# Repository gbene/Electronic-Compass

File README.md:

# Readme

This is the readme file for the Electronic Compass (E.C.) project. This project has the aim to create a low-cost, open-source electronic geological compass. This repository has the objective to document and share the hardware construction process and software development needed. 

The planned compass features are:

+ Measure dip and dip direction of a plane
+ Measure strike slip, trend and plunge
+ Different measures profiles
+ Automatic txt files save
+ Acceletometer and magnetometer calibration
+ More to come!

## Licences
Since the E.C. project covers hardware and software licences that cover both are necessary. You can find the choosen licences in the "Licences folder" in PDF and .txt format.

| Type | License name | Source link | 
| :----: |:----: | :----:|
| **Software** | GNU General Public License v3.0 or later | [SPDX](https://spdx.org/licenses/GPL-3.0-or-later.html) |
| **Hardware** | CERN-OHL-S-2.0 or any later version | [OHWR](https://ohwr.org/cern_ohl_s_v2.txt) |

Table: Licences used

The copyrights to both hardware and software are explicited in the copyright.pdf and copyright.md files and the original copies are stored in the License folder. If you want to apply any kind of change you **always need to log it in the changes.md file** and include all the original source and copyright files as per licences.

## Components list

The Electronic Compass components are searched to be the most cost-effective and easy to solder available that I could find. I provide the links from where the components are purchased but some are europe based (mostly Germany) so check if worldwide shipping is convenient or not.

| Component Name | Quantity | Price | Link |
|:---|:----:|:----:| ---: |
| Adafruit adalogger M0 | x1 | 26€ | [ThePiHut](https://thepihut.com/products/adafruit-feather-m0-adalogger) |
| GY-61 ADXL335 acceletometer | x1 | €6.79 | [AZ-Delivery](https://www.az-delivery.de/en/products/gy-61-adxl335-beschleunigungssensor-3-axis-neigungswinkel-modul-1?variant=20332875546720) |
| 128x32 Oled display | x1 | €6.29 | [AZ-Delivery](https://thepihut.com/products/adafruit-feather-m0-adalogger) |
| GY-271 QMC5883L magnetometer | x1 | €5.79 | [AZ-Delivery](https://www.az-delivery.de/en/products/gy-271-kompassmodul-kompass-magnet-sensor-fuer-arduino-und-raspberry-pi?variant=18912984432736) |
| SD card | x1 | may vary | [Amazon](https://www.amazon.com/)
| 1200mAh 3.7V LiPo battery | x1 | 5.36€ | [Welectron](https://www.welectron.com/LiPo-Pouch-Battery-503562-37V-1200mAh) |
| Potentiometer | x1 | ? | [Amazon](https://www.amazon.com/) |
| Buttons | x? | ? | [Amazon](https://www.amazon.com/) |

Table: Table of components

## Software used

To have a truly open-source project the software used is 100% free and open-source from the CAD project files to the software used to code and flash the code on the adalogger chip.

| Type | Software program | Source link | 
| :----: |:----: | :----:|
| CAD | FreeCAD | [FreeCAD](https://www.freecadweb.org/) |
| Electronics | KiCad EDA| [KiCad](https://kicad.org/) |
| Code environment and upload | ArduinoIDE | [Arduino](https://www.arduino.cc/en/software) |

Table: Software used

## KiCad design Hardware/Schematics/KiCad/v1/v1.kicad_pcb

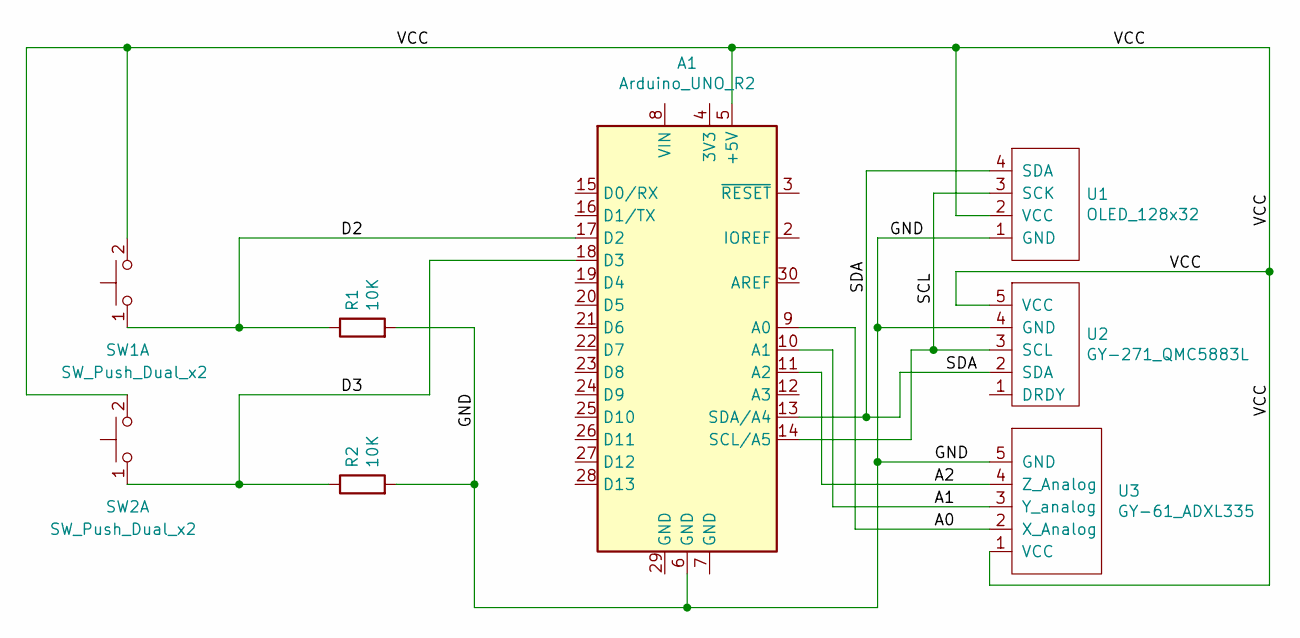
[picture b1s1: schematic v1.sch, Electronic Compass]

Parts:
A1: Arduino_UNO_R2
R1, R2: 10K; R_Axial_DIN0207_L6.3mm_D2.5mm_P7.62mm_Horizontal
SW1, SW2: SW_Push_Dual_x2; SW_PUSH_6mm_H4.3mm
U1: OLED_128x32
U2: GY-271_QMC5883L; GY-271_QMLC5883L
U3: GY-61_ADXL335

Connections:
/A0: A1.9 (A0), U3.2 (X_Analog)
/A1: A1.10 (A1), U3.3 (Y_analog)
/A2: A1.11 (A2), U3.4 (Z_Analog)
/D2: A1.17 (D2), R1.1, SW1.1 (C)
/D3: A1.18 (D3), R2.1, SW2.1 (C)
/GND: A1.6 (GND), R1.2, R2.2, U1.1 (GND), U2.4 (GND), U3.5 (GND)
/SCL: A1.14 (SCL/A5), U1.3 (SCK), U2.3 (SCL)
/SDA: A1.13 (SDA/A4), U1.4 (SDA), U2.2 (SDA)
/VCC: A1.5 (+5V), SW1.2 (D), SW2.2 (D), U1.2 (VCC), U2.5 (VCC), U3.1 (VCC)

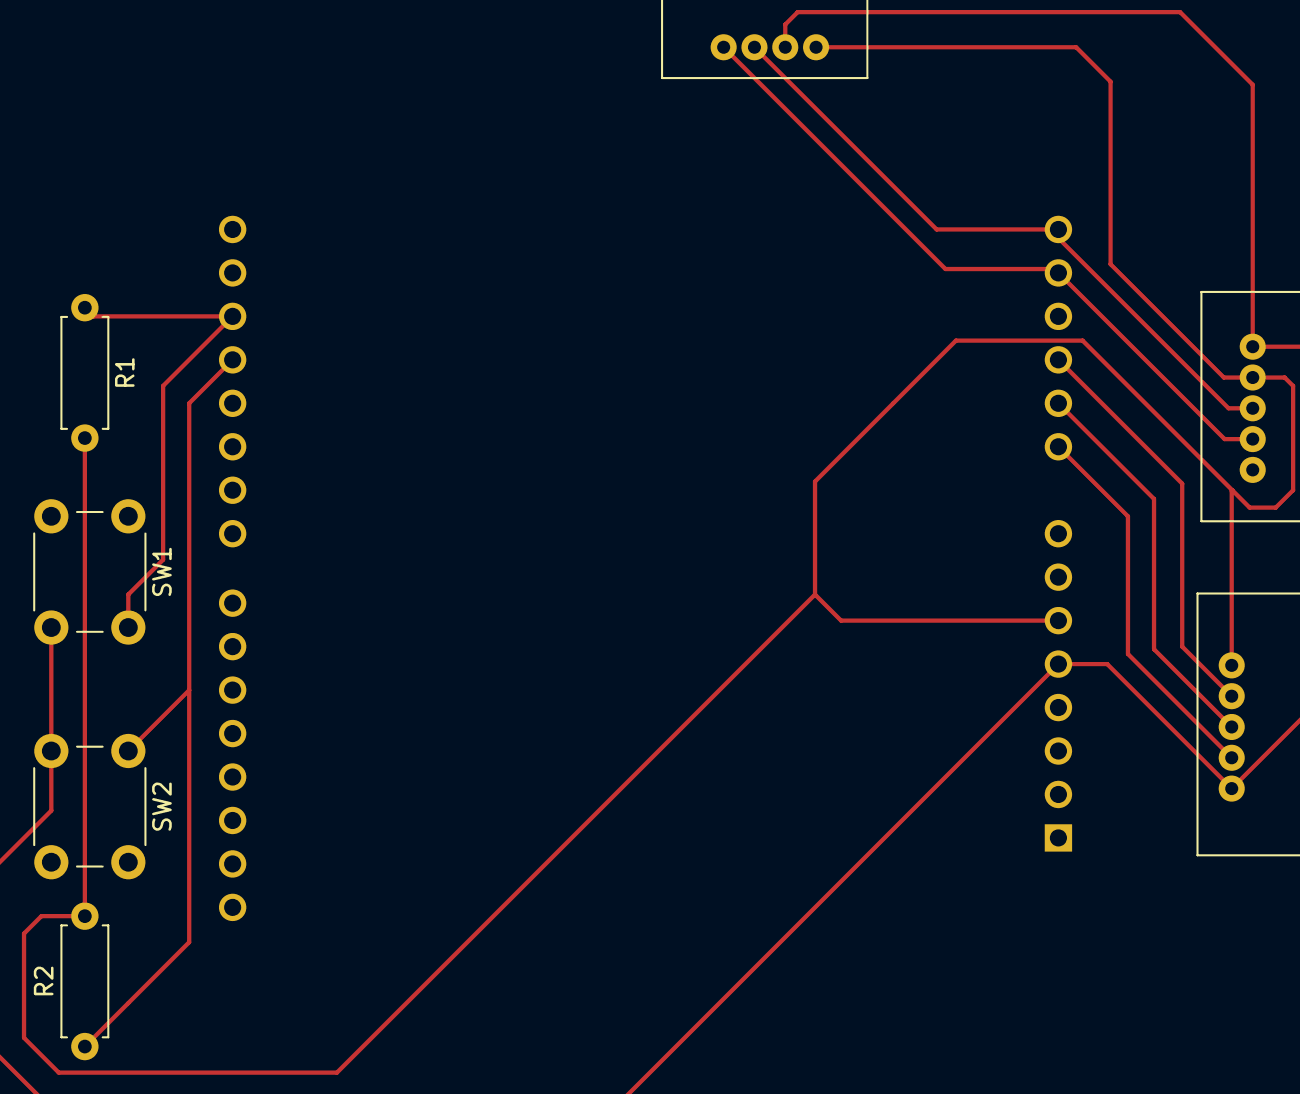
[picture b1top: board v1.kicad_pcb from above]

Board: 2 copper layers, 8 parts (1 on the bottom side), 9 nets.

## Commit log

2020-12-20 Added important files/folders
2020-12-20 Updated source location
2020-12-20 updated COPYRIGHT.pdf
2020-12-20 Added pdf to gitignore
2020-12-23 Addeddbreakout schematics and footprints
2020-12-23 modified gitignore
2020-12-23 V1 wirining schematics and pcb
2020-12-23 fixed adxl pinout
